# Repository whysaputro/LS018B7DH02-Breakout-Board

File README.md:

# LS018B7DH02-Breakout-Board

Breakout board for the **Sharp Memory LCD – LS018B7DH02**. This repository contains **schematics** and **PCB layout** built with **KiCad**, plus fabrication outputs (Gerbers) so you can order boards, assemble, and test quickly.

> **Note:** The LS018B7DH02 is a low-power memory LCD with a simple SPI-like interface. Always verify pinout and operating voltages against the official datasheet for your specific panel.

---
# License
This project is licensed under the **MIT License**.
 
---
# Disclaimer
Design is provided **as-is**, without warranty. Validate against the official **LS018B7DH02 datasheet** and thoroughly test before production.

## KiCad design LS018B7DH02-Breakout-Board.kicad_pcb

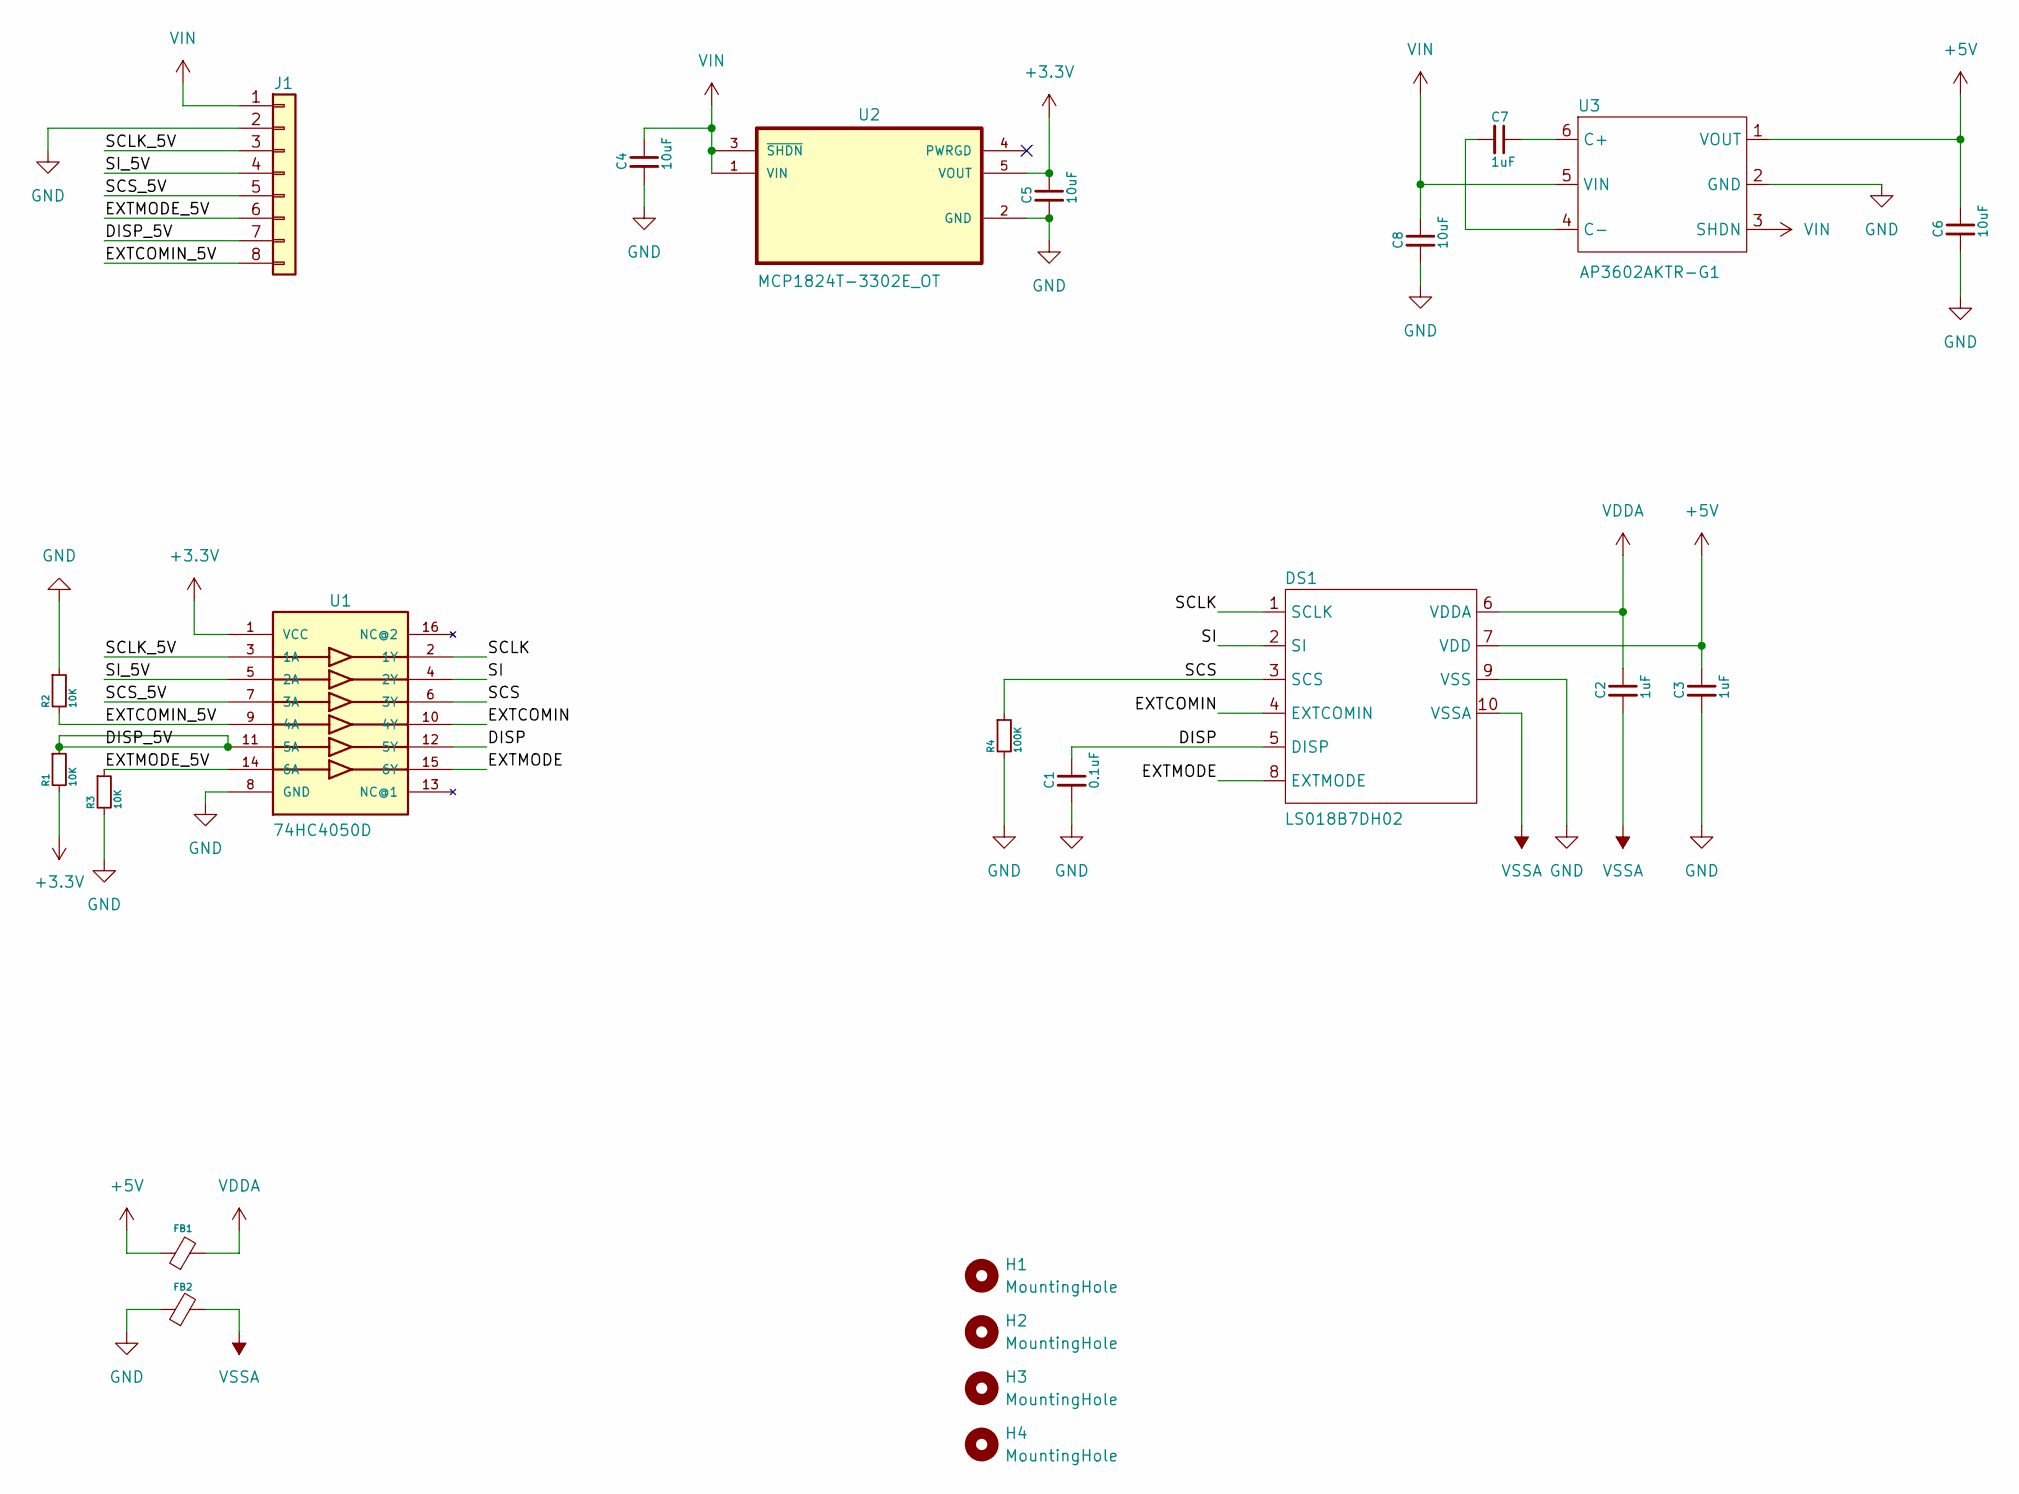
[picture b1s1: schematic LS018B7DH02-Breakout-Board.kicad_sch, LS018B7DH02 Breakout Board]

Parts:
C1: 0.1uF; C_0805_2012Metric_Pad1.18x1.45mm_HandSolder
C2, C3, C7: 1uF; C_0805_2012Metric_Pad1.18x1.45mm_HandSolder
C4, C5, C6, C8: 10uF; C_0805_2012Metric_Pad1.18x1.45mm_HandSolder
DS1: LS018B7DH02; MOLEX_5034801000
FB1, FB2: FerriteBead_Small; L_0805_2012Metric_Pad1.15x1.40mm_HandSolder
H1, H2, H3, H4: MountingHole; MountingHole_3.2mm_M3
J1: Conn_01x08; JST_PH_S8B-PH-SM4-TB_1x08-1MP_P2.00mm_Horizontal
R1, R2, R3: 10K; R_0805_2012Metric_Pad1.20x1.40mm_HandSolder
R4: 100K; R_0805_2012Metric_Pad1.20x1.40mm_HandSolder
U1: 74HC4050D; SO16
U2: MCP1824T-3302E_OT; SOT95P280X145-5N
U3: AP3602AKTR-G1; SOT95P280X145-6N

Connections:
+3.3V: C5.1, R1.2, U1.1 (VCC), U2.5 (VOUT)
+5V: C3.1, C6.1, DS1.7 (VDD), FB1.1, U3.1 (VOUT)
/DISP: C1.1, DS1.5 (DISP), U1.12 (5Y)
/DISP_5V: J1.7, R1.1, U1.11 (5A)
/EXTCOMIN: DS1.4 (EXTCOMIN), U1.10 (4Y)
/EXTCOMIN_5V: J1.8, R2.2, U1.9 (4A)
/EXTMODE: DS1.8 (EXTMODE), U1.15 (6Y)
/EXTMODE_5V: J1.6, R3.1, U1.14 (6A)
/SCLK: DS1.1 (SCLK), U1.2 (1Y)
/SCLK_5V: J1.3, U1.3 (1A)
/SCS: DS1.3 (SCS), R4.1, U1.6 (3Y)
/SCS_5V: J1.5, U1.7 (3A)
/SI: DS1.2 (SI), U1.4 (2Y)
/SI_5V: J1.4, U1.5 (2A)
GND: C1.2, C3.2, C4.2, C5.2, C6.2, C8.2, DS1.9 (VSS), FB2.1, J1.2, R2.1, R3.2, R4.2, U1.8 (GND), U2.2 (GND), U3.2 (GND)
unnamed: C7.1, U3.6 (C+)
unnamed: C7.2, U3.4 (C-)
VDDA: C2.1, DS1.6 (VDDA), FB1.2
VIN: C4.1, C8.1, J1.1, U2.1 (VIN), U2.3 (~SHDN), U3.3 (SHDN), U3.5 (VIN)
VSSA: C2.2, DS1.10 (VSSA), FB2.2

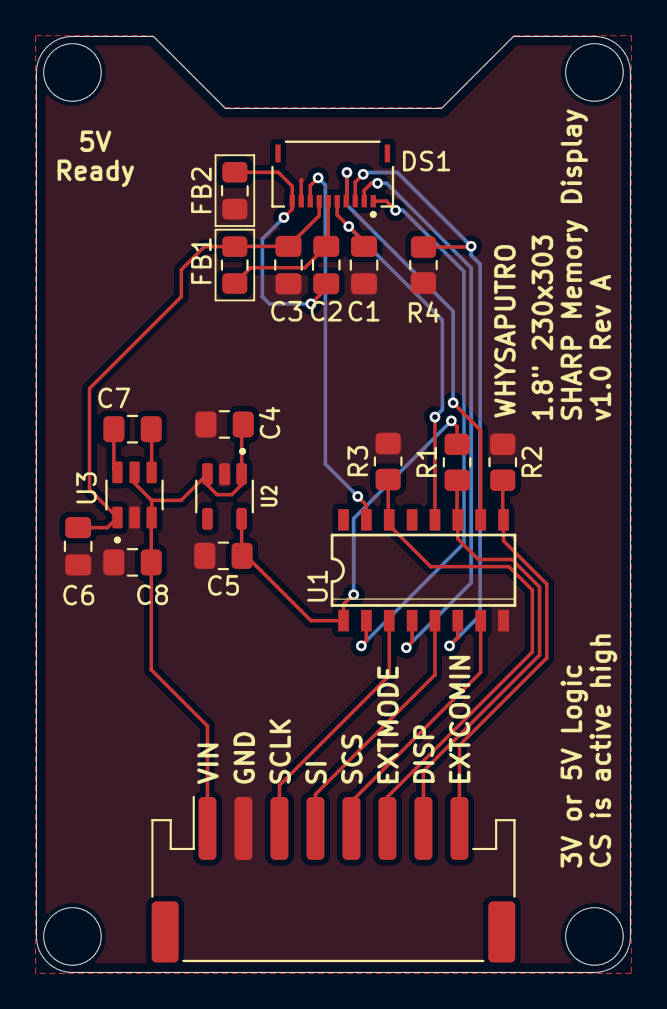
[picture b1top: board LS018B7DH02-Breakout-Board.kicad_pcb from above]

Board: 2 copper layers, 33.0 x 52.0 mm, 23 parts (0 on the bottom side), 20 nets.

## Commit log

2025-11-02 Add MIT license

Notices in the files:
README.md:
License: MIT
